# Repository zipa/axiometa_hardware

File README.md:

# BrodBoost-C

BrodBoost-C is a breadboard power supply that connects via USB Type-C and delivers selectable 5 V and 3.3 V outputs. Its compact design minimizes the need for additional wiring, cable modifications, or bulky bench supplies. The device features independent voltage adjustments for each rail, a manual on/off switch, an LED indicator, and built-in fuse protection, making it a practical solution for projects using standard 2.54 mm breadboards. The 3.3 V regulator is based on the TPS63001, a switching step-down DC-DC converter.

BrodBoost-C is a project of Axiometa, information available on the [website](https://www.axiometa.io/products/brodboost-c-breadboard-power-supply).

# Overview

# Compatibility

# Voltage Selection
Both voltage rails can be independently selected or simultaneously set to 5.0 V or 3.3 V by moving around the jumper cap. Although the jumper cap design has received mixed opinions, it is implemented here as a safety feature and to be cautios of BOM. The design requires deliberate jumper cap movement, which helps prevent accidental voltage changes from 3.3 V to 5.0 V that might occur if a switch were used.

# Schematic
A USB-C receptacle accepts a USB-C cable. The power rails include a series ferrite bead for noise suppression, a 1 A polyfuse for short-circuit protection, and two decoupling capacitors (1 µF and 100 nF). The 5 V from the USB-C port is configured by pulling the CC1 and CC2 lines to ground through 5.1 kΩ resistors.

The power then flows through a series power switch and a parallel red power LED. A step-down conversion from 5 V to 3.3 V is performed using the TPS63001, a switching step-down DC-DC converter.

Both voltage outputs (5.0 V and 3.3 V) are routed to two 1×3 2.54 mm headers, where the middle pin is the selected net and either side may be used for short-circuiting the respective rail. Additionally, a separate header provides access to 5 V, 3.3 V, ground, and USB data lines for debugging, testing, or experimenting with USB data.

# PCB Design
BrodBoost-C is a two-layer PCB measuring 11.4 mm by 54.0 mm, designed to maximize trace width and optimize the switching regulator's ground return path. This layout comfortably supports the nominal device current of approximately 1 A.

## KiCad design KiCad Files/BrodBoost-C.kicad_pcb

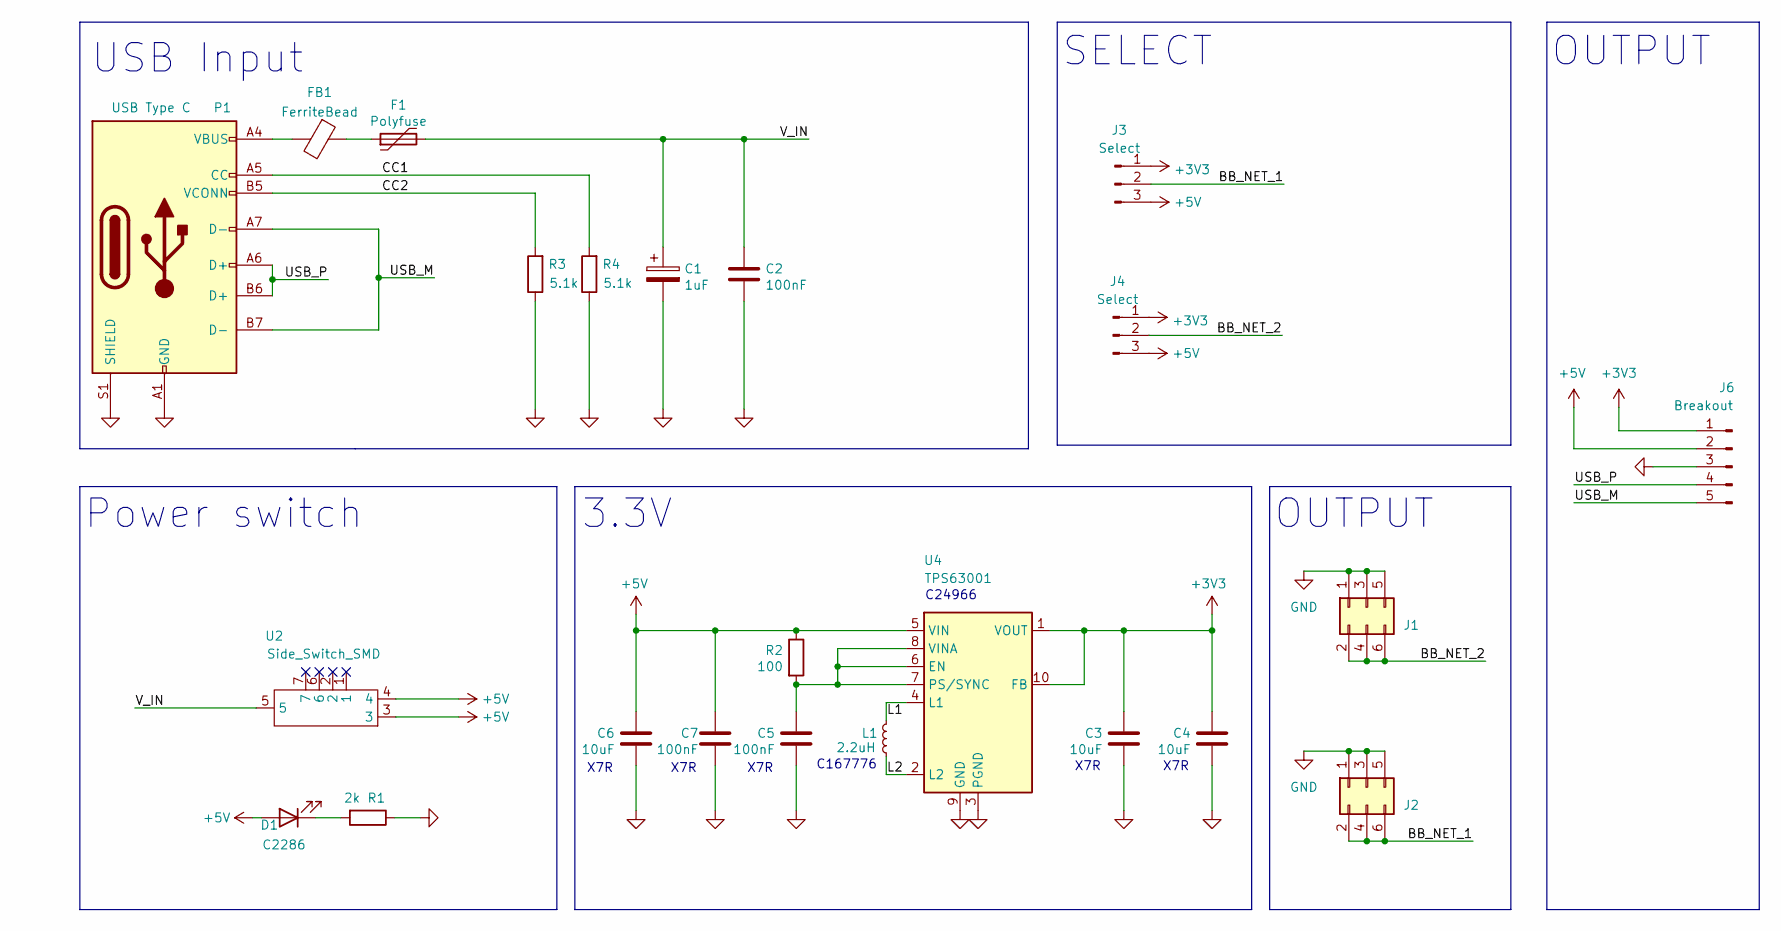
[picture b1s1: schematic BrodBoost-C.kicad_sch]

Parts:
C1: 1uF; C_0402_1005Metric
C2, C5: 100nF; C_0402_1005Metric; JLCPCB C14663
C3, C4, C6: 10uF; C_0603_1608Metric; JLCPCB C14663
C7: 100nF; C_0603_1608Metric; JLCPCB C14663
D1: C2286; LED_0603_1608Metric
F1: Polyfuse; Fuse_1812_4532Metric_Pad1.30x3.40mm_HandSolder
FB1: FerriteBead; C_0805_2012Metric
J1, J2: Conn_02x02_Counter_Clockwise; PinHeader_2x03_P2.54mm_Vertical_SMD
J3, J4: Select; PinHeader_1x03_P2.54mm_Vertical
J6: Breakout
L1: 2.2uH; L_Sunlord_SWPA4012S
P1: USB Type C; USB_C_Receptacle_HRO_TYPE-C-31-M-12
R1: 2k; R_0402_1005Metric
R2: 100; R_0402_1005Metric
R3, R4: 5.1k; R_0402_1005Metric
U2: Side_Switch_SMD; Switch_Side
U4: TPS63001; Texas_DRC0010J_ThermalVias

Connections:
+3V3: C3.1, C4.1, J3.1, J4.1, J6.1, U4.1 (VOUT), U4.10 (FB)
+5V: C6.1, C7.1, D1.2 (A), J3.3, J4.3, J6.2, R2.1, U2.3, U2.4, U4.5 (VIN)
/BB_NET_1: J2.2, J2.4, J2.6, J3.2
/BB_NET_2: J1.2, J1.4, J1.6, J4.2
/CC1: P1.A5 (CC), R4.2
/CC2: P1.B5 (VCONN), R3.2
/L1: L1.2, U4.4 (L1)
/L2: L1.1, U4.2 (L2)
/USB_M: J6.5, P1.A7 (D-), P1.B7 (D-)
/USB_P: J6.4, P1.A6 (D+), P1.B6 (D+)
/V_IN: C1.1, C2.1, F1.2, U2.5
GND: C1.2, C2.2, C3.2, C4.2, C5.2, C6.2, C7.2, J1.1, J1.3, J1.5, J2.1, J2.3, J2.5, J6.3, P1.A1 (GND), P1.A12 (GND), P1.B1 (GND), P1.B12 (GND), P1.S1 (SHIELD), R1.1, R3.1, R4.1, U4.3 (PGND), U4.9 (GND), U4.11 (PGND)
unnamed: D1.1 (K), R1.2
unnamed: F1.1, FB1.1
unnamed: FB1.2, P1.A4 (VBUS), P1.A9 (VBUS), P1.B4 (VBUS), P1.B9 (VBUS)
unnamed: C5.1, R2.2, U4.6 (EN), U4.7 (PS/SYNC), U4.8 (VINA)

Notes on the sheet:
OUTPUT
X7R
Power switch
C167776
3.3V
USB Input
C24966
SELECT

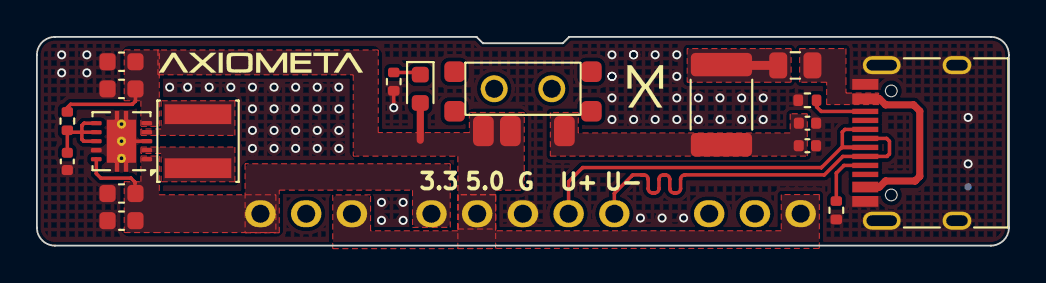
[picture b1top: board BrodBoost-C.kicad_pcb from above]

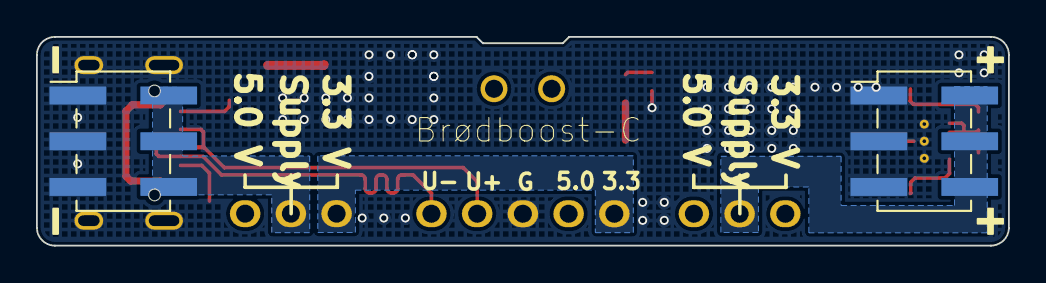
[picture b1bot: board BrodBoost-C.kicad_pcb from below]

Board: 2 copper layers, 54.0 x 11.6 mm, 23 parts (2 on the bottom side), 16 nets.

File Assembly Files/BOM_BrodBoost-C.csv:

Designator,Footprint,Quantity,Value,LCSC Part #
C1,402,1,1uF,C52923
"C2, C5",402,2,100nF,C1525
"C3, C4, C6",603,3,10uF,C19702
C7,603,1,100nF,C14663
D1,603,1,C2286,C2286
F1,1812,1,BSMD1812-110-24V,C883149
FB1,805,1,FerriteBead,C1017
"J1, J2",PinHeader_2x03_P2.54mm_Vertical_SMD,2,Conn_02x02_Counter_Clockwise,C3294461
"J3, J4",PinHeader_1x03_P2.54mm_Vertical,2,Select,C5360899
J6,PinHeader_1x05_P2.54mm_Horizontal,1,Breakout,DNP
L1,L_Sunlord_SWPA4012S,1,2.2uH,C167776
P1,USB_C_Receptacle_HRO_TYPE-C-31-M-12,1,USB Type C,C2927038
R1,402,1,2k,C4109
R2,402,1,100,C25076
"R3, R4",402,2,5.1k,C25905
U2,Switch_Side,1,Side_Switch_SMD,C2911519
U4,Texas_DRC0010J_ThermalVias,1,TPS63001,C28060

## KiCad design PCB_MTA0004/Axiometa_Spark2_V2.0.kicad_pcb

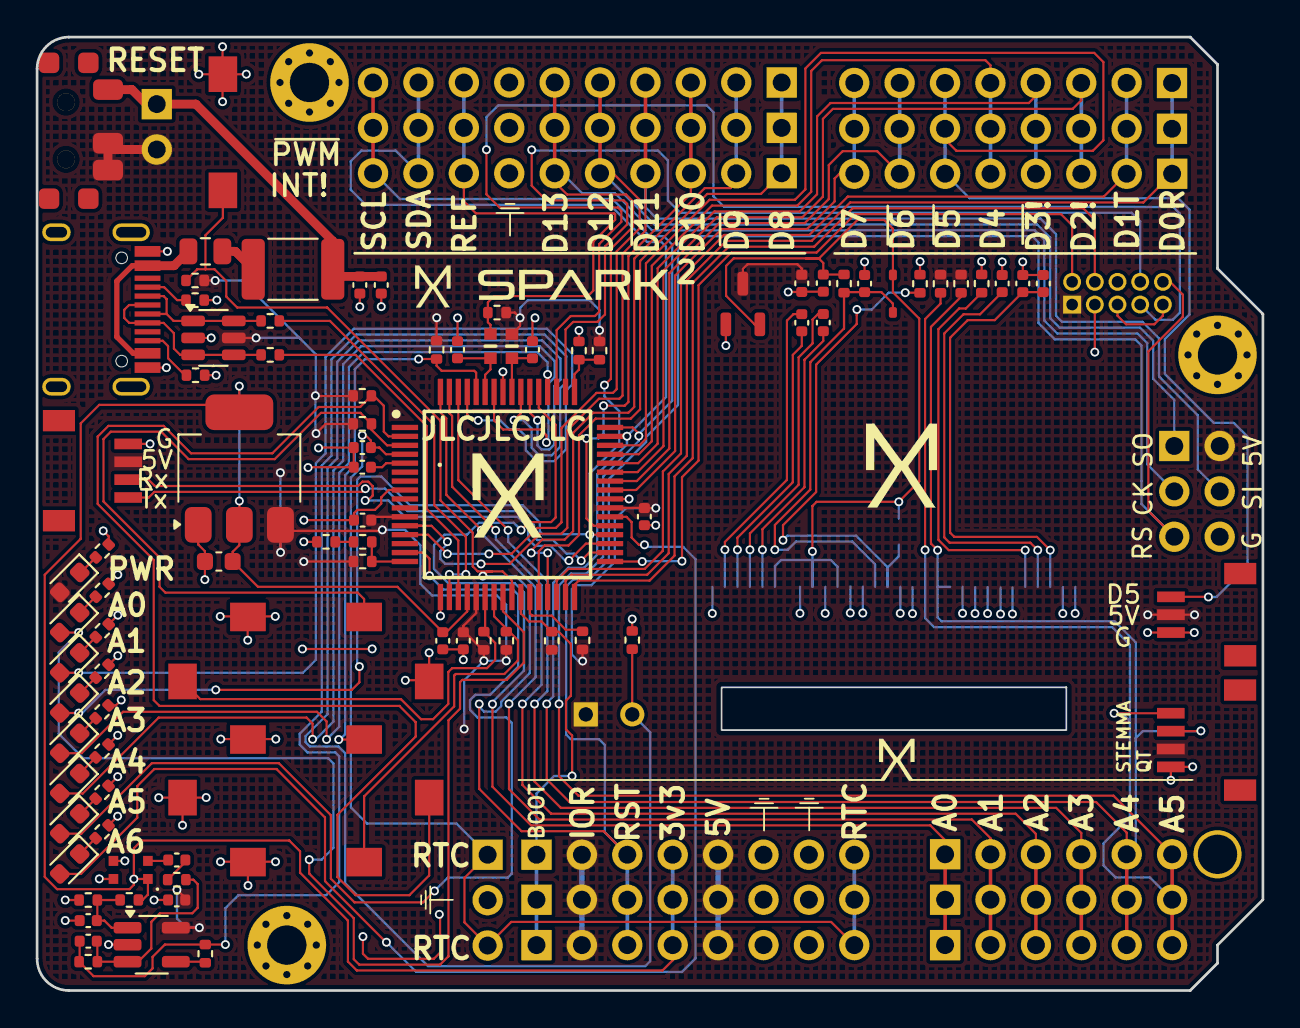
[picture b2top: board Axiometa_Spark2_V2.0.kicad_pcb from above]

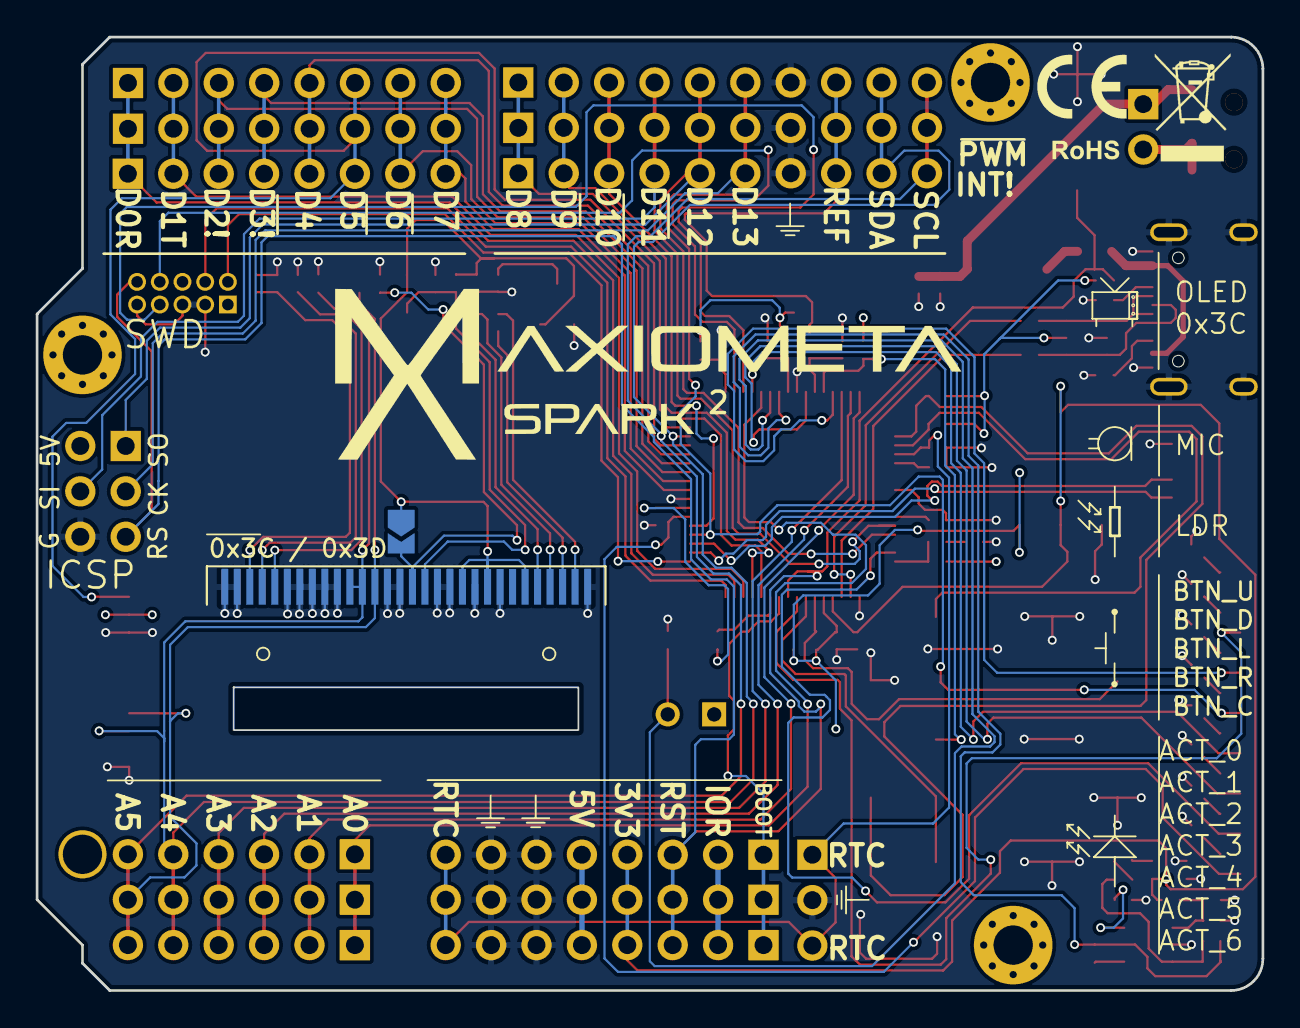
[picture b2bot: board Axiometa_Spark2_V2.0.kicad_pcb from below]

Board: 2 copper layers, 68.6 x 53.3 mm, 109 parts (2 on the bottom side), 85 nets.

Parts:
C1, C11, C21, C25, C26: 1uF; C_0402_1005Metric
C2, C6, C7, C9, C10, C15: 100nF; C_0402_1005Metric
C3, C18, C19, C20: 2.2uF; C_0402_1005Metric
C4, C5, C8, C22: 4.7uF; C_0402_1005Metric
C12: 100pF; C_0402_1005Metric
C13, C14: 10uF; C_0402_1005Metric
C16: 10uF; C_0603_1608Metric
D1, D2, D3, D4, D5, D8, D9: C2290; LED_0603_1608Metric
D6: C2286; LED_0603_1608Metric
D7: 1N4148WS; D_SOD-323
F1: Polyfuse; Fuse_1812_4532Metric_Pad1.30x3.40mm_HandSolder
FB1: FerriteBead; C_0805_2012Metric
FB3, FB4: BLM18PG471SN1D; BLM18SP221SN1B
IC1: R7FA4M1AB3CFM#AA0; QFP50P1200X1200X170-64N
J1, J4, J8, J9, J11, J13: Conn_01x08; PinSocket_1x08_P2.54mm_Vertical
J2, J6, J7: Conn_01x06; PinSocket_1x06_P2.54mm_Vertical
J3, J10, J12: Conn_01x10; PinSocket_1x10_P2.54mm_Vertical
J5: BootLoader; PinHeader_2x03_P2.54mm_Vertical
J14, J17: STEMMA 4 JST-PH; SM04B-SRSS-TB_LFSN_
J16: hph2-a-10-sga; PinHeader_2x05_P1.27mm_Vertical
J18: SSD1306 Display 128x64; OLED_SPARK_R4
J19: Conn_01x03_Pin; JST_SM03B-SRSS-TB_LF__SN_
J20: RTC; PinHeader_1x03_P2.54mm_Vertical
JP3: ADD_SLCT; SolderJumper-2_P1.3mm_Open_TrianglePad1.0x1.5mm
MK1: S15OT421-005; S15OT421
P1: USB Type C; USB_C_Receptacle_HRO_TYPE-C-31-M-12
R1, R2: 22; R_0402_1005Metric
R3, R4, R5, R7, R11, R13, R14, R17, R22: 5.1k; R_0402_1005Metric
R6, R8, R12, R19, R36, R37, R38: 1.5k; R_0402_1005Metric
R9, R23, R30, R31, R32, R33: 10k; R_0402_1005Metric
R10: R_Photo; PinHeader_1x02_P2.00mm_Vertical
R15, R20: 100k; R_0402_1005Metric
R16: 13.7k; R_0402_1005Metric
R18: 100; R_0402_1005Metric
R21, R24, R34, R35: 2k; R_0402_1005Metric
R25: 910k; R_0402_1005Metric
R26, R27, R28, R29: 4.7k; R_0402_1005Metric
SW1, SW3, SW5, SW6, SW7: User Button; SPARK_BUTTON
SW2: Reset; SPARK_BUTTON
SW4: SW_DIP_x01; PinSocket_1x02_P2.54mm_Vertical
U1: LMV321; SOT-23-5_HandSoldering
U2: USBLC6-2SC6; SOT-23-6
U3: AMS1117-3.3V; SOT-223-3_TabPin2
U5: Side_Switch_SMD; Switch_Side
U6: XC6206P332MR-G; SOT-23-3

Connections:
+3V3: C5.1, C16.1, IC1.20 (VCC_USB), J1.4, J8.4, J9.4, MK1.1 (VCC), R35.2, U3.2 (VO)
+5V: C4.1, C6.1, C7.1, C15.1, C25.1, D6.2 (A), FB4.2, IC1.11 (VCC_1), IC1.21 (VCC_USB_LDO), IC1.39 (VCC_2), J1.2, J1.5, J5.2, J8.2, J8.5, J9.2, J9.5, J14.2, J16.1, J17.2, J19.2, R5.2, R7.2, R9.2, R10.1, R11.2, R15.2, R17.1, R22.2, R27.2, R28.2, R30.2, R31.2, R32.2, R33.2, SW4.2, U1.5 (V+), U2.5 (VBUS), U3.3 (VI), U5.3, U5.4, U6.3 (VI)
/MCU/A0: IC1.53 (P014), J2.1, J6.1, J7.1
/MCU/A1: IC1.64 (P000), J2.2, J6.2, J7.2
/MCU/A2: IC1.63 (P001), J2.3, J6.3, J7.3
/MCU/A3: IC1.62 (P002), J2.4, J6.4, J7.4
/MCU/A4: IC1.47 (P101), J2.5, J3.9, J6.5, J7.5, J10.9, J12.9, J17.3, J18.19, J18.20, R27.1
/MCU/A5: IC1.48 (P100), J2.6, J3.10, J6.6, J7.6, J10.10, J12.10, J17.4, J18.18, R28.1
/MCU/ACT_1: D3.2 (A), IC1.52 (P015)
/MCU/ACT_2: D5.2 (A), IC1.58 (P011/VREFL0)
/MCU/ACT_3: D8.2 (A), IC1.15 (P408)
/MCU/ACT_4: D9.2 (A), IC1.38 (P113)
/MCU/AREF: FB3.2, J3.8, J10.8, J12.8, R17.2
/MCU/AT_RX: IC1.31 (P301), J4.1, J11.1, J13.1
/MCU/AT_TX: IC1.30 (P302), J4.2, J11.2, J13.2
/MCU/B1: IC1.22 (P206), R9.1, SW1.1
/MCU/B2: IC1.23 (P205), R30.1, SW5.1
/MCU/B3: IC1.3 (P402), R32.1, SW6.1
/MCU/B4: IC1.2 (P401), R31.1, SW3.1
/MCU/B5: IC1.60 (P004), R33.1, SW7.1
/MCU/BOOT: IC1.26 (P201/MD), J1.1, J8.1, J9.1, R5.1
/MCU/D2: IC1.43 (P105), J4.3, J11.3, J13.3
/MCU/D3: IC1.44 (P104), J4.4, J11.4, J13.4
/MCU/D4: IC1.45 (P103), J4.5, J11.5, J13.5
/MCU/D5: IC1.46 (P102), J4.6, J11.6, J13.6, J19.3
/MCU/D6: IC1.42 (P106), J4.7, J11.7, J13.7
/MCU/D7: IC1.41 (P107), J4.8, J11.8, J13.8
/MCU/D8: IC1.28 (P304), J3.1, J10.1, J12.1
/MCU/D9: IC1.29 (P303), J3.2, J10.2, J12.2
/MCU/D10: IC1.37 (P112), J3.3, J10.3, J12.3
/MCU/LDR: IC1.54 (P013/VREFL), R10.2, R23.2
/MCU/MIC: C12.1, IC1.55 (P012/VREFH), R18.1, R20.2
/MCU/MISO: IC1.13 (P410), J3.5, J5.1, J10.5, J12.5
/MCU/MOSI: IC1.12 (P411), J3.4, J5.4, J10.4, J12.4
/MCU/RESET: IC1.25 (RES), J1.3, J5.5, J8.3, J9.3, J16.10, R22.1, SW2.1
/MCU/RX_2: IC1.35 (P110/TDI), J14.3
/MCU/Rx_LED: D2.2 (A), IC1.24 (P204)
/MCU/SCK: D4.2 (A), IC1.36 (P111), J3.6, J5.3, J10.6, J12.6
/MCU/SWCLK: IC1.32 (P300/TCK/SWCLK), J16.4
/MCU/SWDIO: IC1.33 (P108/TMS/SWDIO), J16.2
/MCU/SWD_RX: IC1.51 (P502), J16.7
/MCU/SWD_TX: IC1.50 (P501), J16.8
/MCU/TX_2: IC1.34 (P109/TDO/SWO), J14.4
/MCU/Tx_LED: D1.2 (A), IC1.61 (P003)
/MCU/USB_D+: IC1.19 (P914/USB_DP), R2.1
/MCU/USB_D-: IC1.18 (P915/USB_DM), R1.1
/MCU/VBATT: C9.1, IC1.4 (VBATT), J1.8, J8.8, J9.8, J20.1, J20.3
/Peripherals/ADDRESS: J18.15, JP3.2 (B), R26.2
/Peripherals/C1N: C18.1, J18.5
/Peripherals/C1P: C18.2, J18.4
/Peripherals/C2N: C3.1, J18.3
/Peripherals/C2P: C3.2, J18.2
/Peripherals/IREF: J18.26, R25.2
/Peripherals/RES: C22.2, D7.2 (A), J18.14, R29.1
/Peripherals/VCC: C26.1, D7.1 (K), J18.6, J18.9, J18.11, JP3.1 (A), R29.2, U6.2 (VO)
/Peripherals/VCOMH: C19.2, J18.27
/USB/CC1: P1.A5 (CC), R4.2
/USB/CC2: P1.B5 (VCONN), R3.2
/USB/V_IN: C1.1, C2.1, F1.2, SW4.1, U5.5
GND: C1.2, C2.2, C4.2, C5.2, C6.2, C7.2, C8.2, C9.2, C10.1, C11.2, C14.2, C15.2, C16.2, C19.1, C20.1, C21.1, C22.1, C25.2, C26.2, IC1.8 (VSS_1), IC1.17 (VSS_USB), IC1.40 (VSS_2), IC1.57 (AVSS0), J1.6, J1.7, J3.7, J5.6, J8.6, J8.7, J9.6, J9.7, J10.7, J12.7, J14.1, J16.3, J16.5, J16.9, J17.1, J18.1, J18.8, J18.10, J18.12, J18.13, J18.16, J18.17, J18.21, J18.22, J18.23, J18.24, J18.25, J18.29, J18.30, J19.1, J20.2, MK1.2 (GND), MK1.3 (GND), P1.A1 (GND), P1.A12 (GND), P1.B1 (GND), P1.B12 (GND), P1.S1 (SHIELD), R3.1, R4.1, R6.1, R8.1, R12.2, R14.1, R16.1, R19.2, R23.1, R24.1, R25.1, R26.1, R34.2, R36.2, R37.2, R38.2, SW1.2, SW2.2, SW3.2, SW5.2, SW6.2, SW7.2, U1.2 (V-), U2.2 (GND), U3.1 (GND), U6.1 (GND)
unnamed: C13.2, R21.1
unnamed: D1.1 (K), R6.2
unnamed: D2.1 (K), R8.2
unnamed: D3.1 (K), R19.1
unnamed: D4.1 (K), R12.1
unnamed: D5.1 (K), R36.1
unnamed: D6.1 (K), R24.2
unnamed: D8.1 (K), R37.1
unnamed: D9.1 (K), R38.1
unnamed: F1.1, FB1.1
unnamed: FB1.2, P1.A4 (VBUS), P1.A9 (VBUS), P1.B4 (VBUS), P1.B9 (VBUS)
unnamed: C11.1, FB4.1, IC1.56 (AVCC0)
unnamed: C10.2, FB3.1, IC1.59 (P010/VREFH0)
unnamed: IC1.27 (P200), R7.1
unnamed: IC1.16 (P407), R11.1, R13.2
unnamed: IC1.49 (P500), R15.1, R16.2
unnamed: C8.1, IC1.5 (VCL)
unnamed: C20.2, C21.2, J18.28
unnamed: C13.1, MK1.4 (OUT)
unnamed: P1.A6 (D+), P1.B6 (D+), R2.2, U2.3 (I/O2), U2.4 (I/O2)
unnamed: P1.A7 (D-), P1.B7 (D-), R1.2, U2.1 (I/O1), U2.6 (I/O1)
unnamed: R13.1, R14.2
unnamed: R18.2, U1.4
unnamed: C14.1, R34.1, R35.1, U1.1 (+)
unnamed: C12.2, R20.1, R21.2, U1.3 (-)

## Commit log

2024-01-22 Rename Axiometa_City_Test.ino to Axiometa_City_DevOnly.ino
2024-02-22 Update Axiometa_City_DevOnly.ino
    added logo
2024-08-18 Create Axiometa City 2
2024-08-18 Update Axiometa City 2
2024-12-29 Axiometa Spark 2
2024-12-29 name chnages
2024-12-29 added files
2025-01-04 deleted old hierarachy
2025-01-04 name changes
2025-01-04 moved files to a folder
2025-01-04 added breadboost-c
2025-02-02 hiearachy
2025-02-02 hirearchy
2025-02-02 hierarchy
2025-02-02 added assembly files
2025-02-02 added kicad project
2025-02-02 added quick access schematic
2025-02-02 added schematics and 3d model
2025-02-02 delted lone pdf
2025-02-02 renamed
2025-02-02 Create LICENSE file with CERN-OHL-S
    Copied text from https://ohwr.org/cern_ohl_s_v2.txt
    Closes: issue #1.
